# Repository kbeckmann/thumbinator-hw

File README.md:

# thumbinator

Thumb-sized USB to I2C and SPI bridge

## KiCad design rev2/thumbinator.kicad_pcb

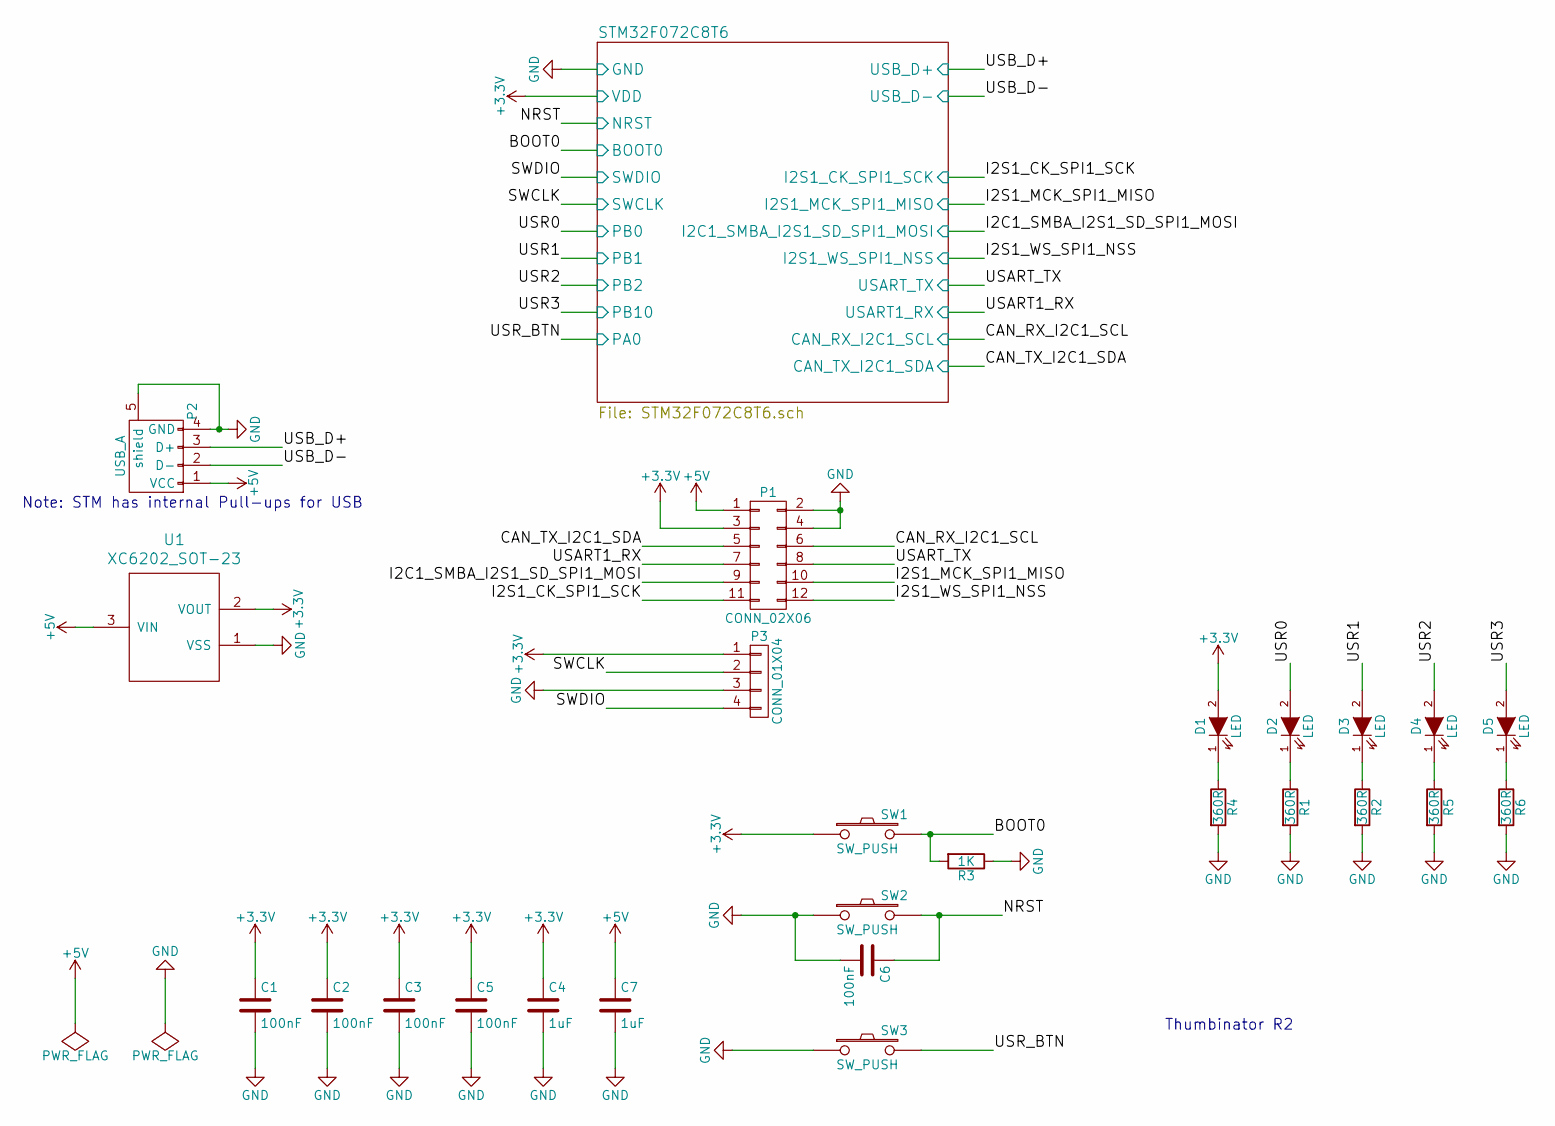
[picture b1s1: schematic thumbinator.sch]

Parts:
C1, C2, C3, C5, C6: 100nF; C_0603
C4, C7: 1uF; C_0603
D1, D2, D3, D4, D5: LED; LED_0603
P1: CONN_02X06; Pin_Header_Straight_2x06
P2: USB_A; USB_Type_A_SMD_Male_G49
P3: CONN_01X04; Pin_Header_Straight_1x04
R1, R2, R4, R5, R6: 360R; R_0603
R3: 1K; R_0603
SW1, SW2, SW3: SW_PUSH; SmallButton
U1: XC6202_SOT-23; SOT-23

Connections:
+3V3: C1.1, C2.1, C3.1, C4.1, C5.1, D1.2 (A), P1.3, P3.1, SW1.1, U1.2 (VOUT); also elsewhere on the board
+5V: C7.1, P1.1, P2.1 (VCC), U1.3 (VIN)
/BOOT0: R3.2, SW1.2; also elsewhere on the board
/CAN_RX_I2C1_SCL: P1.6; also elsewhere on the board
/CAN_TX_I2C1_SDA: P1.5; also elsewhere on the board
/I2C1_SMBA_I2S1_SD_SPI1_MOSI: P1.9; also elsewhere on the board
/I2S1_CK_SPI1_SCK: P1.11; also elsewhere on the board
/I2S1_MCK_SPI1_MISO: P1.10; also elsewhere on the board
/I2S1_WS_SPI1_NSS: P1.12; also elsewhere on the board
/NRST: C6.1, SW2.2; also elsewhere on the board
/SWCLK: P3.2; also elsewhere on the board
/SWDIO: P3.4; also elsewhere on the board
/USART1_RX: P1.7; also elsewhere on the board
/USART_TX: P1.8; also elsewhere on the board
/USB_D+: P2.3 (D+); also elsewhere on the board
/USB_D-: P2.2 (D-); also elsewhere on the board
/USR0: D2.2 (A); also elsewhere on the board
/USR1: D3.2 (A); also elsewhere on the board
/USR2: D4.2 (A); also elsewhere on the board
/USR3: D5.2 (A); also elsewhere on the board
/USR_BTN: SW3.2; also elsewhere on the board
GND: C1.2, C2.2, C3.2, C4.2, C5.2, C6.2, C7.2, P1.2, P1.4, P2.4 (GND), P2.5 (shield), P3.3, R1.2, R2.2, R3.1, R4.2, R5.2, R6.2, SW2.1, SW3.1, U1.1 (VSS); also elsewhere on the board
unnamed: D1.1 (K), R4.1
unnamed: D2.1 (K), R1.1
unnamed: D3.1 (K), R2.1
unnamed: D4.1 (K), R5.1
unnamed: D5.1 (K), R6.1

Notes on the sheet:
Note: STM has internal Pull-ups for USB
Thumbinator R2

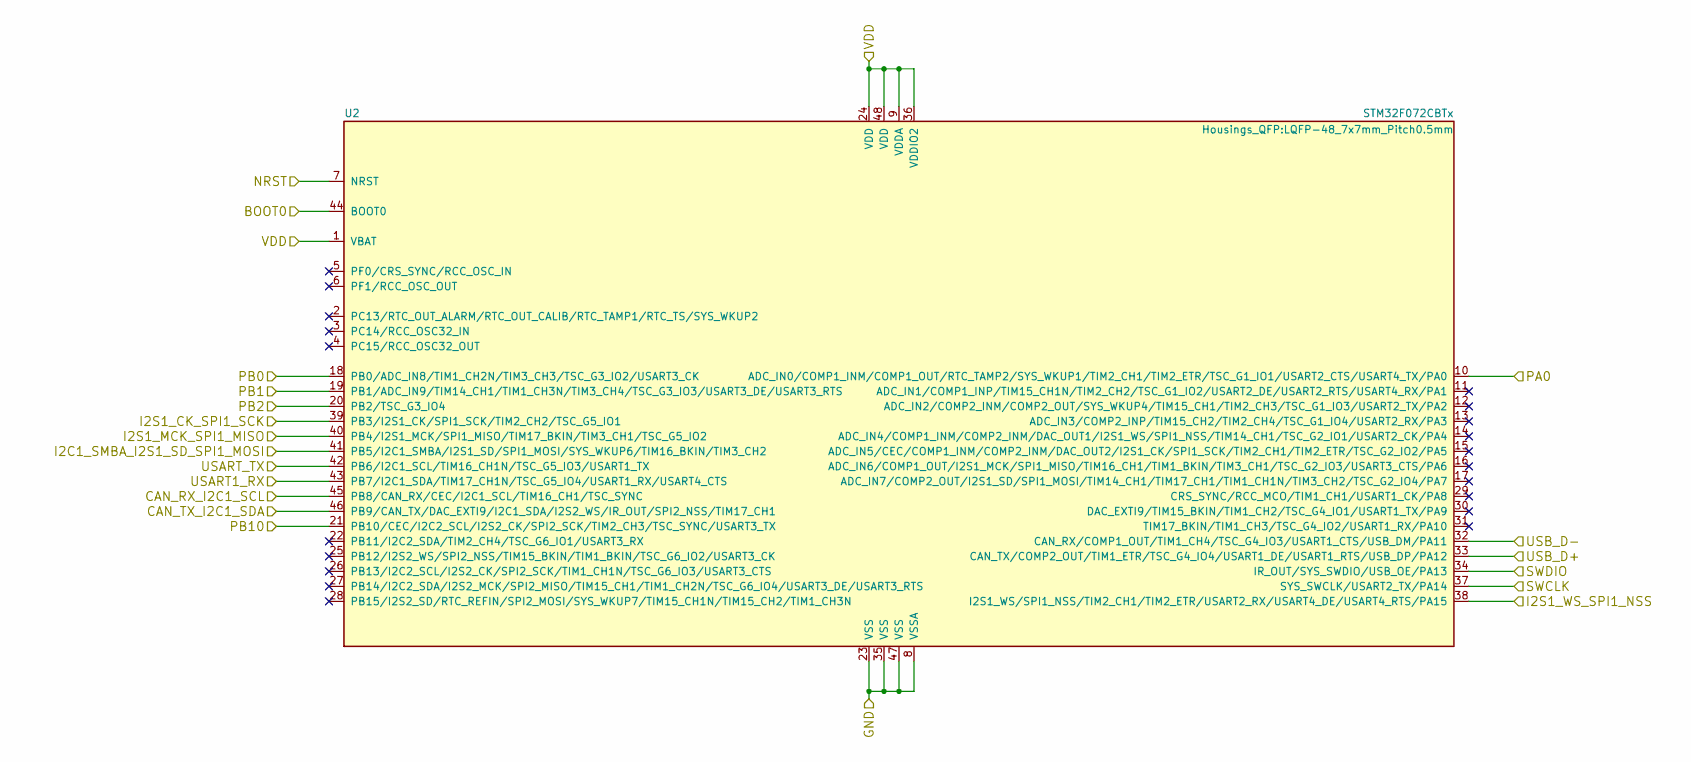
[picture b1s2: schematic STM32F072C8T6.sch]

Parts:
U2: STM32F072CBTx; LQFP-48_7x7mm_Pitch0.5mm

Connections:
+3V3: U2.1 (VBAT), U2.9 (VDDA), U2.24 (VDD), U2.36 (VDDIO2), U2.48 (VDD); also elsewhere on the board
/BOOT0: U2.44 (BOOT0); also elsewhere on the board
/CAN_RX_I2C1_SCL: U2.45 (PB8/CAN_RX/CEC/I2C1_SCL/TIM16_CH1/TSC_S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); also elsewhere on the board
/CAN_TX_I2C1_SDA: U2.46 (PB9/CAN_TX/DAC_EXTI9/I2C1_SDA/I2S2_WS/I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); also elsewhere on the board
/I2C1_SMBA_I2S1_SD_SPI1_MOSI: U2.41 (PB5/I2C1_SMBA/I2S1_SD/SPI1_MOSI/SYS_WKU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); also elsewhere on the board
/I2S1_CK_SPI1_SCK: U2.39 (PB3/I2S1_CK/SPI1_SCK/TIM2_CH2/TSC_G5_IO1); also elsewhere on the board
/I2S1_MCK_SPI1_MISO: U2.40 (PB4/I2S1_MCK/SPI1_MISO/TIM17_BKIN/TIM3_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); also elsewhere on the board
/I2S1_WS_SPI1_NSS: U2.38 (I2S1_WS/SPI1_NSS/TIM2_CH1/TIM2_ETR/USAR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); also elsewhere on the board
/NRST: U2.7 (NRST); also elsewhere on the board
/SWCLK: U2.37 (SYS_SWCLK/USART2_TX/PA14); also elsewhere on the board
/SWDIO: U2.34 (IR_OUT/SYS_SWDIO/USB_OE/PA13); also elsewhere on the board
/USART1_RX: U2.43 (PB7/I2C1_SDA/TIM17_CH1N/TSC_G5_IO4/USAR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); also elsewhere on the board
/USART_TX: U2.42 (PB6/I2C1_SCL/TIM16_CH1N/TSC_G5_IO3/USAR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); also elsewhere on the board
/USB_D+: U2.33 (CAN_TX/COMP2_OUT/TIM1_ETR/TSC_G4_IO4/US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); also elsewhere on the board
/USB_D-: U2.32 (CAN_RX/COMP1_OUT/TIM1_CH4/TSC_G4_IO3/US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); also elsewhere on the board
/USR0: U2.18 (PB0/ADC_IN8/TIM1_CH2N/TIM3_CH3/TSC_G3_I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); also elsewhere on the board
/USR1: U2.19 (PB1/ADC_IN9/TIM14_CH1/TIM1_CH3N/TIM3_CH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); also elsewhere on the board
/USR2: U2.20 (PB2/TSC_G3_IO4); also elsewhere on the board
/USR3: U2.21 (PB10/CEC/I2C2_SCL/I2S2_CK/SPI2_SCK/TIM2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); also elsewhere on the board
/USR_BTN: U2.10 (ADC_IN0/COMP1_INM/COMP1_OUT/RTC_TAMP2/S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); also elsewhere on the board
GND: U2.8 (VSSA), U2.23 (VSS), U2.35 (VSS), U2.47 (VSS); also elsewhere on the board

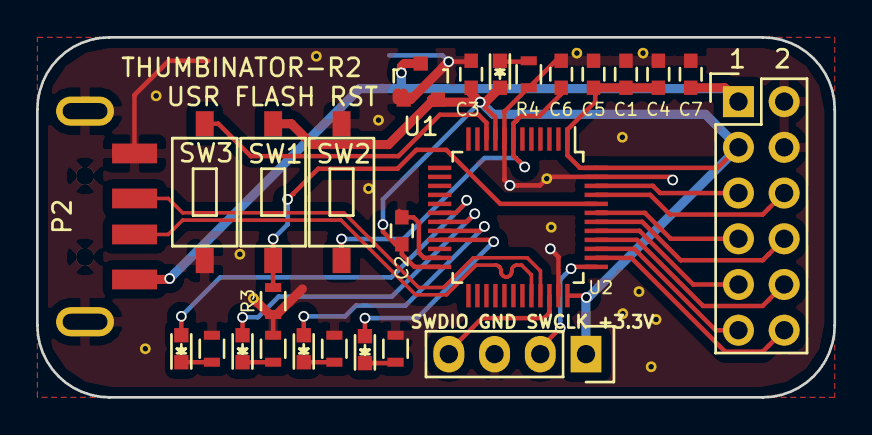
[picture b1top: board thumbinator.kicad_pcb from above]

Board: 2 copper layers, 44.3 x 20.0 mm, 26 parts (0 on the bottom side), 27 nets.

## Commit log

2016-10-02 First stab at the hardware
2016-10-02 PCB polishing
2016-10-02 Tweaking
2016-10-02 Soon done
2016-10-02 Logos etc
2016-10-02 Thumbinator r1
2016-10-02 Add missing file
2016-10-02 cross platform
2016-10-02 Fixed model
2016-11-13 Rev2
    - Changed LDO to XC6202 SOT-23
    - Changed buttons to 3x6mm
    - Made board a tiny bit smaller
2017-02-09 Add BOM
2017-02-14 Add BOM and zipped BOM
2017-02-21 Add pdf schematic
